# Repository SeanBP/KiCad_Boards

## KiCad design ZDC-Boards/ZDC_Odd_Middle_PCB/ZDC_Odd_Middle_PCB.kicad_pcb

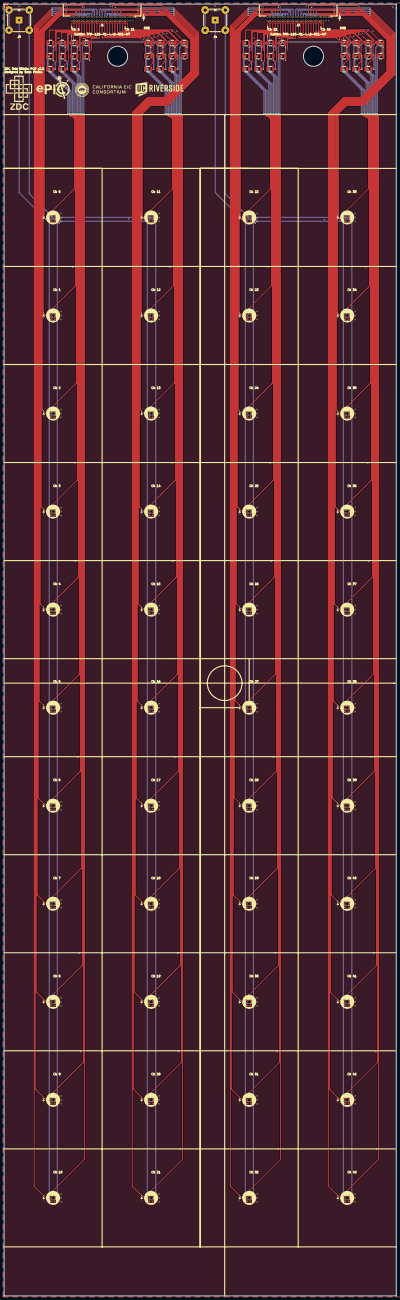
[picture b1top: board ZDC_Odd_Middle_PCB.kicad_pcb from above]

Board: 2 copper layers, 195.2 x 643.0 mm, 92 parts (0 on the bottom side), 91 nets.

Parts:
C0, C1, C2, C3, C4, C5, C6, C7, C8, C9, C10, C11, C12, C13, C14, C15, C16, C17, C18, C19, C20, C21, C22, C23, C24, C25, C26, C27, C28, C29, C30, C31, C32, C33, C34, C35, C36, C37, C38, C39, C40, C41, C42, C43: C_1210_3225Metric
D0, D1, D2, D3, D4, D5, D6, D7, D8, D9, D10, D11, D12, D13, D14, D15, D16, D17, D18, D19, D20, D21, D22, D23, D24, D25, D26, D27, D28, D29, D30, D31, D32, D33, D34, D35, D36, D37, D38, D39, D40, D41, D42, D43: S14160-3015PS; S14160-1315PS_dimple_silkscreen_with_capacitor
J1, J2: Samtec_TFM-125-01-x-D-RE1-WT_2x25_P1.27mm_Horizon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; Samtec_TFM-125-01-x-D-RE1-WT_2x25_P1.27mm_Horizontal
J3: BNC_TEConnectivity_1478035_Horizontal; BNC_TEConnectivity_1478035_Horizontal_EdgePads
J4: BNC_TEConnectivity_1478035_Horizontal

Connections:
A0: D0.8, J1.49
A1: D1.8, J1.47
A2: D2.8, J1.45
A3: D3.8, J1.43
A4: D4.8, J1.41
A5: D5.8, J1.39
A6: D6.8, J1.37
A7: D7.8, J1.35
A8: D8.8, J1.33
A9: D9.8, J1.31
A10: D10.8, J1.29
A11: D11.8, J1.27
A12: D12.8, J1.25
A13: D13.8, J1.23
A14: D14.8, J1.21
A15: D15.8, J1.19
A16: D16.8, J1.17
A17: D17.8, J1.15
A18: D18.8, J1.13
A19: D19.8, J1.11
A20: D20.8, J1.9
A21: D21.8, J1.7
A22: D22.8, J2.49
A23: D23.8, J2.47
A24: D24.8, J2.45
A25: D25.8, J2.43
A26: D26.8, J2.41
A27: D27.8, J2.39
A28: D28.8, J2.37
A29: D29.8, J2.35
A30: D30.8, J2.33
A31: D31.8, J2.31
A32: D32.8, J2.29
A33: D33.8, J2.27
A34: D34.8, J2.25
A35: D35.8, J2.23
A36: D36.8, J2.21
A37: D37.8, J2.19
A38: D38.8, J2.17
A39: D39.8, J2.15
A40: D40.8, J2.13
A41: D41.8, J2.11
A42: D42.8, J2.9
A43: D43.8, J2.7
GND: C0.2, C1.2, C2.2, C3.2, C4.2, C5.2, C6.2, C7.2, C8.2, C9.2, C10.2, C11.2, C12.2, C13.2, C14.2, C15.2, C16.2, C17.2, C18.2, C19.2, C20.2, C21.2, C22.2, C23.2, C24.2, C25.2, C26.2, C27.2, C28.2, C29.2, C30.2, C31.2, C32.2, C33.2, C34.2, C35.2, C36.2, C37.2, C38.2, C39.2, C40.2, C41.2, C42.2, C43.2, J1.1, J1.MP, J2.1, J2.MP
K0: C0.1, D0.7, J1.50
K1: C1.1, D1.7, J1.48
K2: C2.1, D2.7, J1.46
K3: C3.1, D3.7, J1.44
K4: C4.1, D4.7, J1.42
K5: C5.1, D5.7, J1.40
K6: C6.1, D6.7, J1.38
K7: C7.1, D7.7, J1.36
K8: C8.1, D8.7, J1.34
K9: C9.1, D9.7, J1.32
K10: C10.1, D10.7, J1.30
K11: C11.1, D11.7, J1.28
K12: C12.1, D12.7, J1.26
K13: C13.1, D13.7, J1.24
K14: C14.1, D14.7, J1.22
K15: C15.1, D15.7, J1.20
K16: C16.1, D16.7, J1.18
K17: C17.1, D17.7, J1.16
K18: C18.1, D18.7, J1.14
K19: C19.1, D19.7, J1.12
K20: C20.1, D20.7, J1.10
K21: C21.1, D21.7, J1.8
K22: C22.1, D22.7, J2.50
K23: C23.1, D23.7, J2.48
K24: C24.1, D24.7, J2.46
K25: C25.1, D25.7, J2.44
K26: C26.1, D26.7, J2.42
K27: C27.1, D27.7, J2.40
K28: C28.1, D28.7, J2.38
K29: C29.1, D29.7, J2.36
K30: C30.1, D30.7, J2.34
K31: C31.1, D31.7, J2.32
K32: C32.1, D32.7, J2.30
K33: C33.1, D33.7, J2.28
K34: C34.1, D34.7, J2.26
K35: C35.1, D35.7, J2.24
K36: C36.1, D36.7, J2.22
K37: C37.1, D37.7, J2.20
K38: C38.1, D38.7, J2.18
K39: C39.1, D39.7, J2.16
K40: C40.1, D40.7, J2.14
K41: C41.1, D41.7, J2.12
K42: C42.1, D42.7, J2.10
K43: C43.1, D43.7, J2.8
LA1: D0.9, D1.9, D2.9, D3.9, D4.9, D5.9, D6.9, D7.9, D8.9, D9.9, D10.9, D11.9, D12.9, D13.9, D14.9, D15.9, D16.9, D17.9, D18.9, D19.9, D20.9, D21.9, J3.1
LA2: D22.9, D23.9, D24.9, D25.9, D26.9, D27.9, D28.9, D29.9, D30.9, D31.9, D32.9, D33.9, D34.9, D35.9, D36.9, D37.9, D38.9, D39.9, D40.9, D41.9, D42.9, D43.9, J4.1

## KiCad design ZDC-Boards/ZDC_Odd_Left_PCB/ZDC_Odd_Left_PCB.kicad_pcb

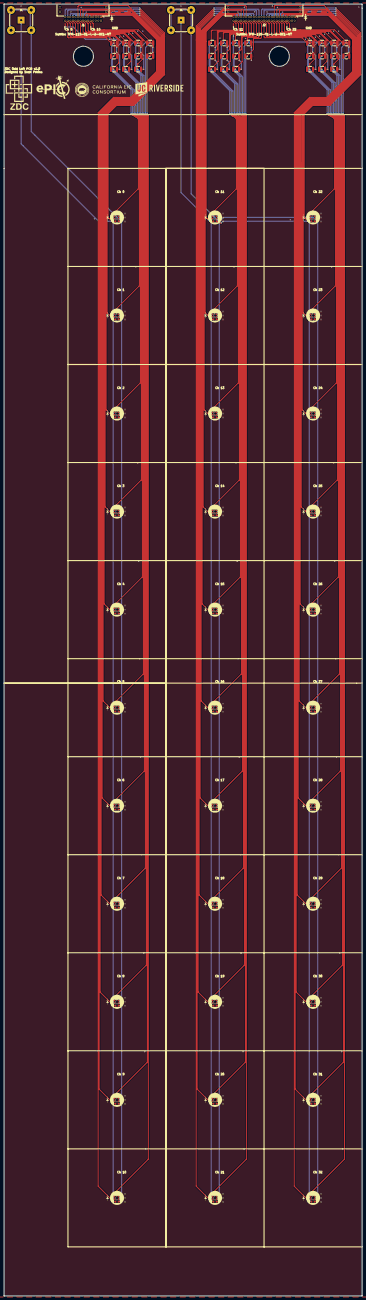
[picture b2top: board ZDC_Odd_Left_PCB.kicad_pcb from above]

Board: 2 copper layers, 178.2 x 643.0 mm, 70 parts (0 on the bottom side), 69 nets.

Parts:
C0, C1, C2, C3, C4, C5, C6, C7, C8, C9, C10, C11, C12, C13, C14, C15, C16, C17, C18, C19, C20, C21, C22, C23, C24, C25, C26, C27, C28, C29, C30, C31, C32: C_1210_3225Metric
D0, D1, D2, D3, D4, D5, D6, D7, D8, D9, D10, D11, D12, D13, D14, D15, D16, D17, D18, D19, D20, D21, D22, D23, D24, D25, D26, D27, D28, D29, D30, D31, D32: S14160-3015PS; S14160-1315PS_dimple_silkscreen_with_capacitor
J1: Samtec_TFM-115-01-x-D-RE1-WT_2x15_P1.27mm_Horizon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; Samtec_TFM-115-01-x-D-RE1-WT_2x15_P1.27mm_Horizontal
J2: Samtec_TFM-125-01-x-D-RE1-WT_2x25_P1.27mm_Horizon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; Samtec_TFM-125-01-x-D-RE1-WT_2x25_P1.27mm_Horizontal
J3, J4: BNC_TEConnectivity_1478035_Horizontal

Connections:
A0: D0.8, J1.29
A1: D1.8, J1.27
A2: D2.8, J1.25
A3: D3.8, J1.23
A4: D4.8, J1.21
A5: D5.8, J1.19
A6: D6.8, J1.17
A7: D7.8, J1.15
A8: D8.8, J1.13
A9: D9.8, J1.11
A10: D10.8, J1.9
A11: D11.8, J2.49
A12: D12.8, J2.47
A13: D13.8, J2.45
A14: D14.8, J2.43
A15: D15.8, J2.41
A16: D16.8, J2.39
A17: D17.8, J2.37
A18: D18.8, J2.35
A19: D19.8, J2.33
A20: D20.8, J2.31
A21: D21.8, J2.29
A22: D22.8, J2.27
A23: D23.8, J2.25
A24: D24.8, J2.23
A25: D25.8, J2.21
A26: D26.8, J2.19
A27: D27.8, J2.17
A28: D28.8, J2.15
A29: D29.8, J2.13
A30: D30.8, J2.11
A31: D31.8, J2.9
A32: D32.8, J2.7
GND: C0.2, C1.2, C2.2, C3.2, C4.2, C5.2, C6.2, C7.2, C8.2, C9.2, C10.2, C11.2, C12.2, C13.2, C14.2, C15.2, C16.2, C17.2, C18.2, C19.2, C20.2, C21.2, C22.2, C23.2, C24.2, C25.2, C26.2, C27.2, C28.2, C29.2, C30.2, C31.2, C32.2, J1.1, J1.MP, J2.1, J2.MP
K0: C0.1, D0.7, J1.30
K1: C1.1, D1.7, J1.28
K2: C2.1, D2.7, J1.26
K3: C3.1, D3.7, J1.24
K4: C4.1, D4.7, J1.22
K5: C5.1, D5.7, J1.20
K6: C6.1, D6.7, J1.18
K7: C7.1, D7.7, J1.16
K8: C8.1, D8.7, J1.14
K9: C9.1, D9.7, J1.12
K10: C10.1, D10.7, J1.10
K11: C11.1, D11.7, J2.50
K12: C12.1, D12.7, J2.48
K13: C13.1, D13.7, J2.46
K14: C14.1, D14.7, J2.44
K15: C15.1, D15.7, J2.42
K16: C16.1, D16.7, J2.40
K17: C17.1, D17.7, J2.38
K18: C18.1, D18.7, J2.36
K19: C19.1, D19.7, J2.34
K20: C20.1, D20.7, J2.32
K21: C21.1, D21.7, J2.30
K22: C22.1, D22.7, J2.28
K23: C23.1, D23.7, J2.26
K24: C24.1, D24.7, J2.24
K25: C25.1, D25.7, J2.22
K26: C26.1, D26.7, J2.20
K27: C27.1, D27.7, J2.18
K28: C28.1, D28.7, J2.16
K29: C29.1, D29.7, J2.14
K30: C30.1, D30.7, J2.12
K31: C31.1, D31.7, J2.10
K32: C32.1, D32.7, J2.8
LA1: D0.9, D1.9, D2.9, D3.9, D4.9, D5.9, D6.9, D7.9, D8.9, D9.9, D10.9, J3.1
LA2: D11.9, D12.9, D13.9, D14.9, D15.9, D16.9, D17.9, D18.9, D19.9, D20.9, D21.9, D22.9, D23.9, D24.9, D25.9, D26.9, D27.9, D28.9, D29.9, D30.9, D31.9, D32.9, J4.1

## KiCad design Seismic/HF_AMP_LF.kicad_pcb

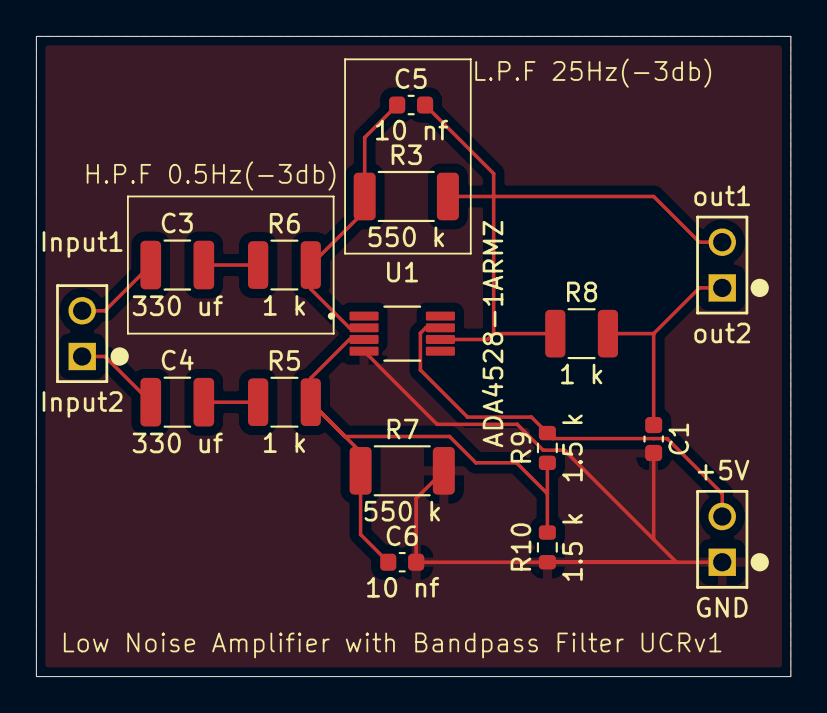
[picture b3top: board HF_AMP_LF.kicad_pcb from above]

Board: 2 copper layers, 41.9 x 35.6 mm, 13 parts (0 on the bottom side), 8 nets.

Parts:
C1: 1 uf; C_0603_1608Metric
C3, C4: 330 uf; C_1210_3225Metric
C5, C6: 10 nf; C_0603_1608Metric
R3, R7: 550 k; R_2010_5025Metric
R5, R6, R8: 1 k; R_1210_3225Metric
R9, R10: 1.5 k; R_0603_1608Metric
U1: ADA4528-1ARMZ; SOP65P490X110-8N

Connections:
+5V: R9.2, U1.7 (V+)
GND: C1.2, C6.2, R7.2, R10.1, U1.4 (V-)
unnamed: C1.1, R8.2
unnamed: C3.2, R6.1
unnamed: C4.2, R5.1
unnamed: C6.1, R5.2, R7.1, R9.1, R10.2, U1.3 (+IN)
unnamed: C5.1, R3.1, R6.2, U1.2 (-IN)
unnamed: C5.2, R3.2, R8.1, U1.6 (OUT)

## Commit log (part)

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2025-05-28 Updated PCBs to include temp sensors
2025-05-28 Finished CAEN adapter
2025-06-06 Updated boards
2025-08-08 Adding boards
2025-09-08 Updated boards with connector HSEC8-109-01-L-DV-A-BL
2025-09-08 Updated board names and images
2025-09-08 Added prototype boards
2025-09-09 Added CAEN-8ch-Old
2025-09-12 Fixed Gamma-32ch-3in
2025-10-10 Added CAEN-8ch-80mm
2025-10-10 Updated names for "old" CAEN adapters
2025-10-10 Added Muon-8ch-48.8mm-2mmSiPM
2025-10-10 Updated silkscreen with proper SiPM number S13360-2050VE
2025-10-14 Edge Card 9ch v2 + 9ch latch IV board v2 +
    Updated Edge Card 9ch to v2 with expanded pads, and fixed 9ch latch IV board to reroute one trace around a hole
2025-10-17 Fixed CAEN-8ch-80mm disconnected traces
2025-10-31 Added Edge-Card-CAEN
2026-01-26 Upload RJ45 connector boards and 16ch board with small tile.
2026-02-20 Included zip file with gerber outputs.
2026-02-20 Edge Card gerber file added
2026-03-25 Corrected channel 5 connection
2026-03-25 Fixed Samtec 10-pin connector for pinned sipms.
2026-04-01 Filter+Amplifier Board for reading sesmic output and output to Pi
2026-04-01 Included links to the model of the board used.
2026-04-03 fixed jlcpcb version
2026-06-17 Updated ZDC Boards to v1.0
2026-06-25 Updated small connector on ZDC PCBs
